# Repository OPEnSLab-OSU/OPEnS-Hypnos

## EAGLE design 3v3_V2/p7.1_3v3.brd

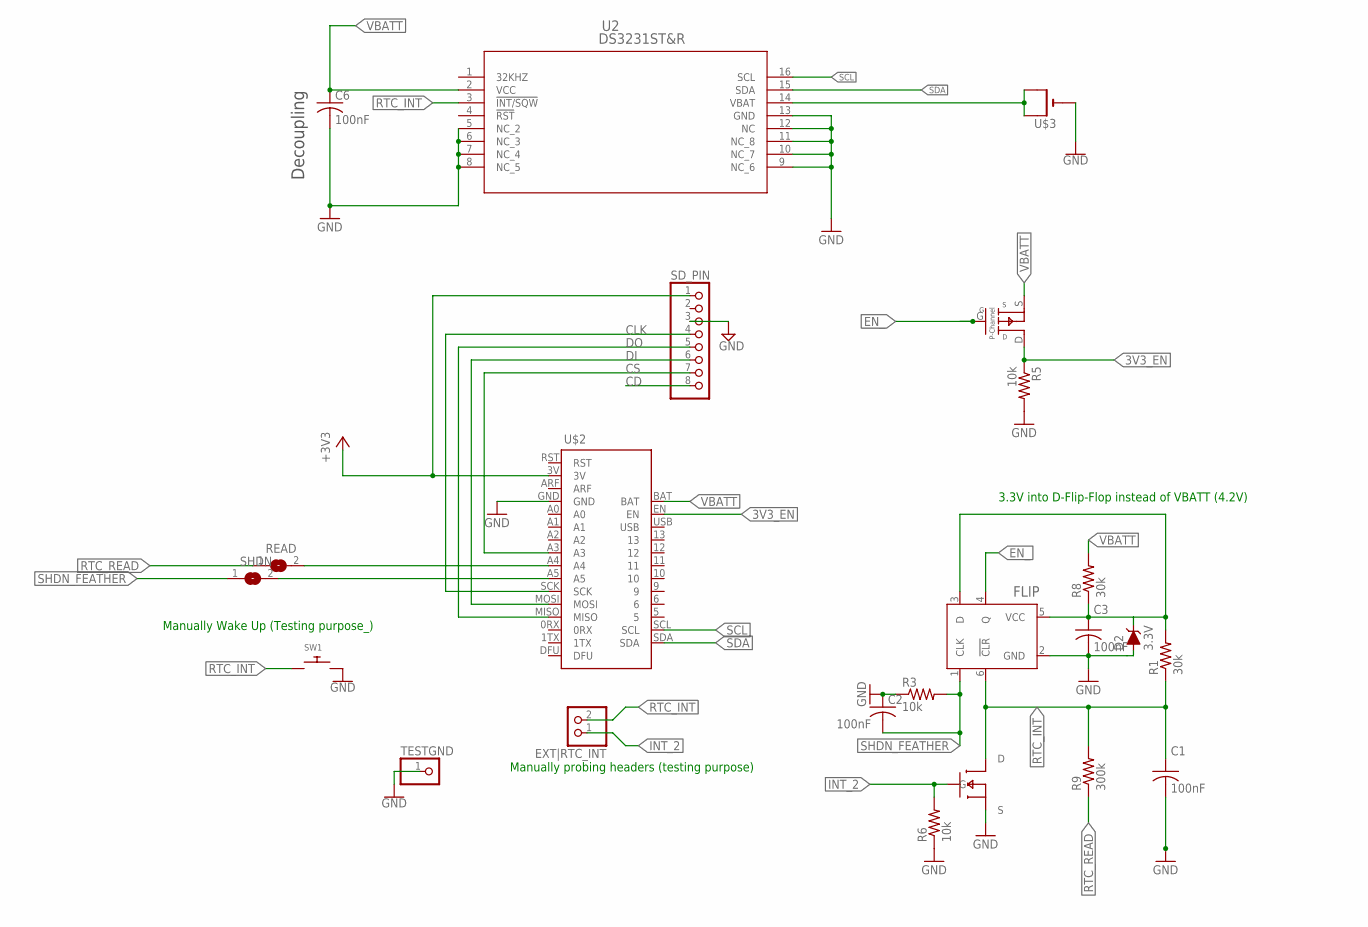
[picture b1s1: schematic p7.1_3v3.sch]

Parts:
C1, C2, C3, C6: 100nF; C1206
D2: 3.3V; SOD-323
EXT|RTC_INT: PINHD-1X2; 1X02
FLIP: SN74LVC1G175DBVR; DBV6
PMOS: MOSFET-SOT23F; SOT-23F
Q2: SSM3J3228R; SOT-23-3
R1, R8: 30k; R1206
R3, R5, R6: 10k; R1206
R9: 300k; R1206
READ: SJ
SD_PIN: PINHD-1X8BIG; 1X08-BIG
SHDN: SJ
SW1: SWITCH_PUSHBUTTONSOFTTOUCHSMD_SJ; PUSHBUTTON_SMD_SJ
TESTGND: PINHD-1X1; 1X01
U2: DS3231ST&R; 21-0042B_16
U$2: BLUEFRUIT_M0; BLUEFRUIT_MO
U$3: CR1220SMT; CR1220-SMD

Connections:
3V3_EN: Q2.D, R5.1, U$2.EN
+3V3: SD_PIN.1, U$2.3V
CD: SD_PIN.8
CLK: SD_PIN.4, U$2.SCK
CS: SD_PIN.7, U$2.A3
DI: SD_PIN.6, U$2.MOSI
DO: SD_PIN.5, U$2.MISO
EN_: FLIP.4 (Q), Q2.G
GND: C2.1, C3.2, C6.2, D2.A, FLIP.2 (GND), PMOS.S, R3.1, R5.2, R6.1, SD_PIN.3, SW1.P$2, TESTGND.1, U2.5 (NC_2), U2.6 (NC_3), U2.7 (NC_4), U2.8 (NC_5), U2.9 (NC_6), U2.10 (NC_7), U2.11 (NC_8), U2.12 (NC), U2.13 (GND), U$2.GND, U$3.-
INT_2: EXT|RTC_INT.1, PMOS.G, R6.2
unnamed: U2.14 (VBAT), U$3.+$1 (+), U$3.+$2 (+1)
unnamed: SHDN.2, U$2.A5
unnamed: READ.2, U$2.A4
unnamed: C3.1, D2.C, FLIP.3 (D), FLIP.5 (VCC), R1.2, R8.1
RTC_INT: C1.1, EXT|RTC_INT.2, FLIP.6 (!CLR), PMOS.D, R1.1, R9.2, SW1.P$1, U2.3 (!INT/SQW)
RTC_READ: R9.1, READ.1
SCL: U2.16 (SCL), U$2.SCL
SDA: U2.15 (SDA), U$2.SDA
SHDN_FEATHER: C2.2, FLIP.1 (CLK), R3.2, SHDN.1
VBATT: C6.1, Q2.S, R8.2, U2.2 (VCC), U$2.BAT

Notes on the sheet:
Decoupling
3.3V into D-Flip-Flop instead of VBATT (4.2V)
Manually Wake Up (Testing purpose_)
Manually probing headers (testing purpose)

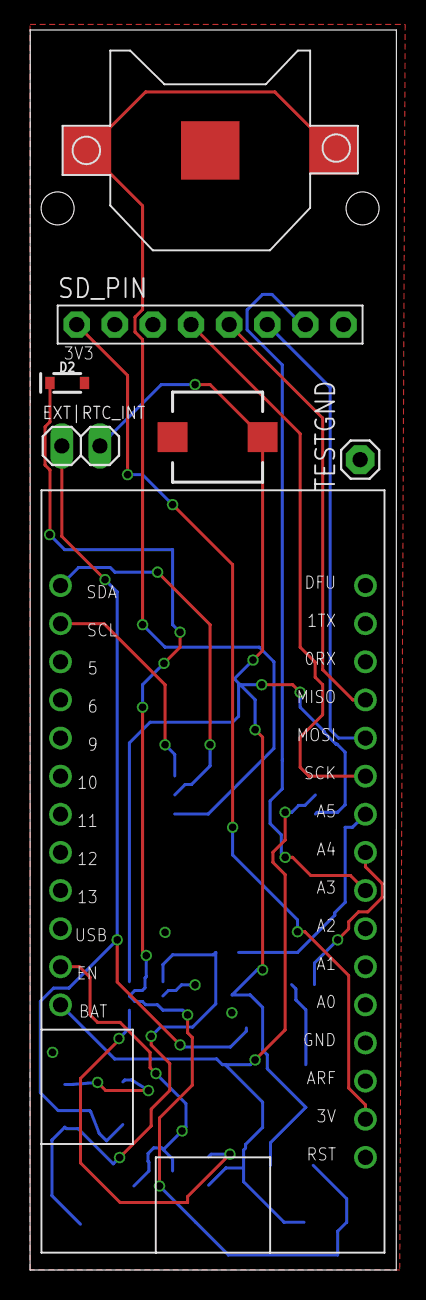
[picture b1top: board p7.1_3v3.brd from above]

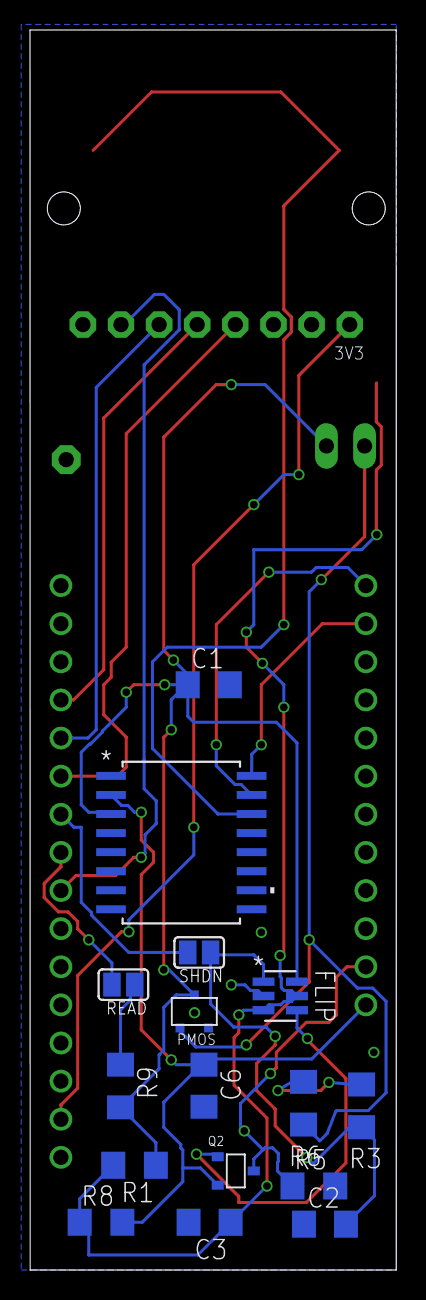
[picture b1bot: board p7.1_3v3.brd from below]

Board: 2 copper layers, 24.4 x 82.6 mm, 23 parts (16 on the bottom side), 19 nets.

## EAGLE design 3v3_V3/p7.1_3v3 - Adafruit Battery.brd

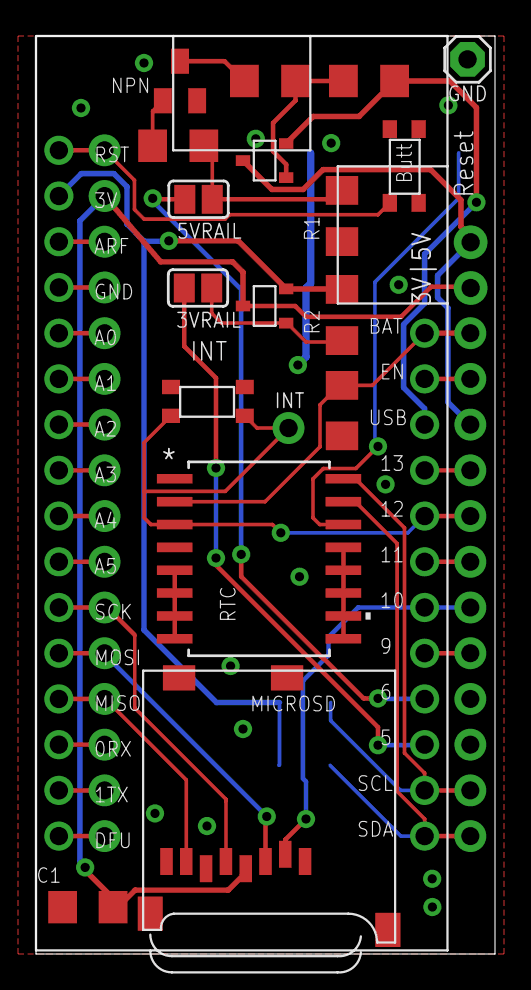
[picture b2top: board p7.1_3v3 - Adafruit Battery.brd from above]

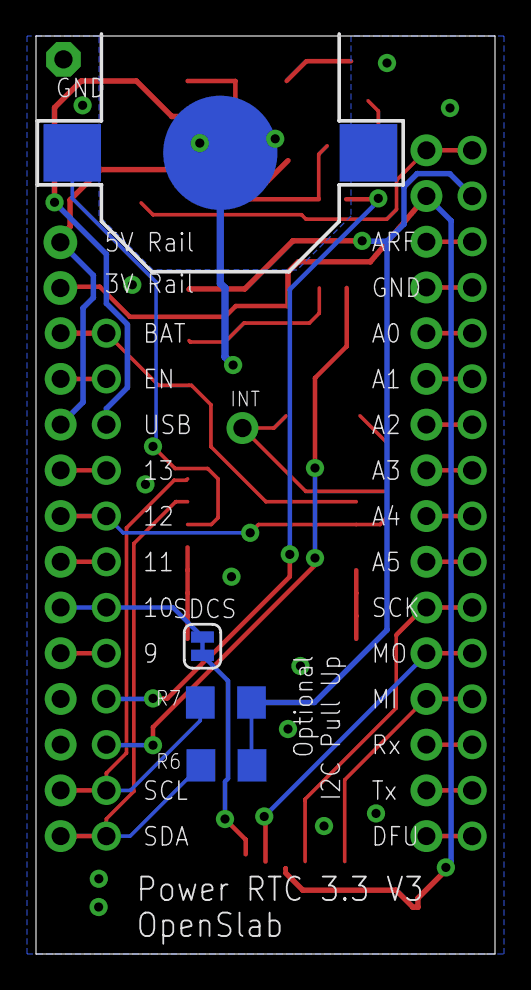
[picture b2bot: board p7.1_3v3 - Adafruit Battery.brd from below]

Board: 2 copper layers, 25.5 x 51.0 mm, 25 parts (5 on the bottom side), 37 nets.

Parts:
3VRAIL, 5VRAIL: SJ
3V|5V: 1X02_NO_SILK
B1: CR1220
C1, C3: 100nF; C1206
CS: SD Select; SMT-JUMPER_2_NC_TRACE_SILK
FEATHER: BLUEFRUIT_M0; BLUEFRUIT_MO
GND: 1X01
INT: 1X01-CLEANBIG
MICROSD: MICROSD
MS1: FEATHERWING
NPN: SOT23
PMOS1, PMOS2: SSM3J3228R; SOT-23-3
R1, R2: 30k; R1206
R3: 2M; R1206
R4: 80k; R1206
R5: 20k; R1206
R6, R7: 10k; R1206
RTC: DS3231ST&R; 21-0042B_16
U$1, U$2: PUSH_BUTTON; PUSHBUTTON_SMD

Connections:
0RX: FEATHER.0RX, MS1.14
1TX: FEATHER.1TX, MS1.15
3VRAIL: 3V|5V.1, C1.1, MICROSD.4, MS1.2, PMOS2.D
5VRAIL: 3V|5V.2, MS1.26, PMOS1.D
5VUSB: FEATHER.USB, PMOS1.S, R4.1
9: FEATHER.9, MS1.21
11: FEATHER.11, MS1.23
13: FEATHER.13, MS1.25
+3V3: FEATHER.3V, PMOS2.S, R2.2, R6.1, R7.1
A0: FEATHER.A0, MS1.5
A1: FEATHER.A1, MS1.6
A2: FEATHER.A2, MS1.7
A3: FEATHER.A3, MS1.8
A4: FEATHER.A4, MS1.9
A5: FEATHER.A5, MS1.10
ARF: FEATHER.ARF, MS1.3
CLK: FEATHER.SCK, MICROSD.5, MS1.11
CS: CS.2, MICROSD.2
DFU: FEATHER.DFU, MS1.16
DI: FEATHER.MOSI, MICROSD.3, MS1.12
DO: FEATHER.MISO, MICROSD.7, MS1.13
EN: FEATHER.EN, MS1.27
GND: B1.-, C1.2, C3.2, FEATHER.GND, GND.1, MICROSD.6, MICROSD.MT1, MICROSD.MT2, MS1.4, NPN.2, R1.2, RTC.5, RTC.6, RTC.7, RTC.8, RTC.9, RTC.10, RTC.11, RTC.12, RTC.13, U$1.1, U$1.2, U$2.3, U$2.4
unnamed: 5VRAIL.1, FEATHER.6
unnamed: B1.+$1, RTC.14
unnamed: 3VRAIL.1, FEATHER.5
unnamed: 5VRAIL.2, R1.1, R3.1
unnamed: 3VRAIL.2, PMOS2.G, R2.1
unnamed: NPN.1, R3.2
unnamed: NPN.3, R5.2
unnamed: PMOS1.G, R4.2, R5.1
unnamed: CS.1, FEATHER.10, MS1.22
RESET: FEATHER.RST, MS1.1, U$1.3, U$1.4
RTC_INT: FEATHER.12, INT.1, MS1.24, RTC.3, U$2.1, U$2.2
SCL: FEATHER.SCL, MS1.18, R7.2, RTC.16
SDA: FEATHER.SDA, MS1.17, R6.2, RTC.15
VBATT: C3.1, FEATHER.BAT, MS1.28, RTC.2

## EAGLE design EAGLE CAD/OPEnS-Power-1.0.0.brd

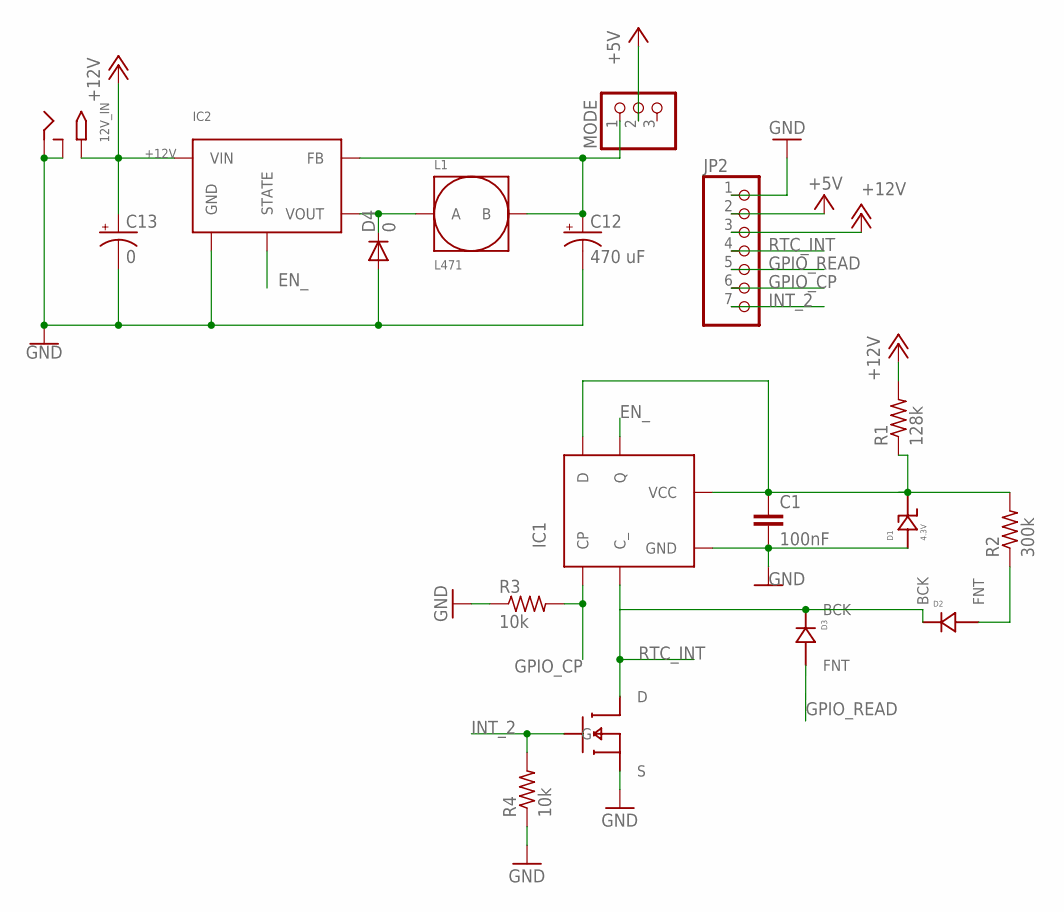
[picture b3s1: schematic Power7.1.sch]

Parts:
12V_IN: 2.1MMJACKSMT; DCJACK_2MM_SMT
C1: 100nF; C0805
C12: 470 uF; 153CLV-0810
C13: 0; 153CLV-0505
D1: 4.3V; DO-219AC
D2, D3: DIODE-DO-214AC
D4: 0; DO41-10
IC1: NC7SZ175; SC70
IC2: LM2575; TO-263
JP2: PINHD-1X7; 1X07
L1: L471; 12-12
MODE: PINHD-1X3; 1X03
Q1: MOSFET-SOT23F; SOT-23F
R1: 128k; R0805
R2: 300k; R0805
R3, R4: 10k; R0805

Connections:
5_RAW: C12.+, IC2.FB, L1.B, MODE.1
+5V: JP2.2, MODE.2
+12V: 12V_IN.PWR2 (TIP), C13.+, IC2.VIN, JP2.3, R1.2
EN_: IC1.Q, IC2.STATE
GND: 12V_IN.GND (RING), 12V_IN.GNDBREAK (RING_SW), C1.2, C12.-, C13.-, D1.BCK, D4.A, IC1.GND, IC2.GND, JP2.1, Q1.S, R3.1, R4.1
GPIO_CP: IC1.CP, JP2.6, R3.2
GPIO_READ: D3.FNT, JP2.5
INT_2: JP2.7, Q1.G, R4.2
unnamed: D4.C, IC2.VOUT, L1.A
unnamed: C1.1, D1.FNT, IC1.D, IC1.VCC, R1.1, R2.2
unnamed: D2.FNT, R2.1
RTC_INT: D2.BCK, D3.BCK, IC1.C_, JP2.4, Q1.D

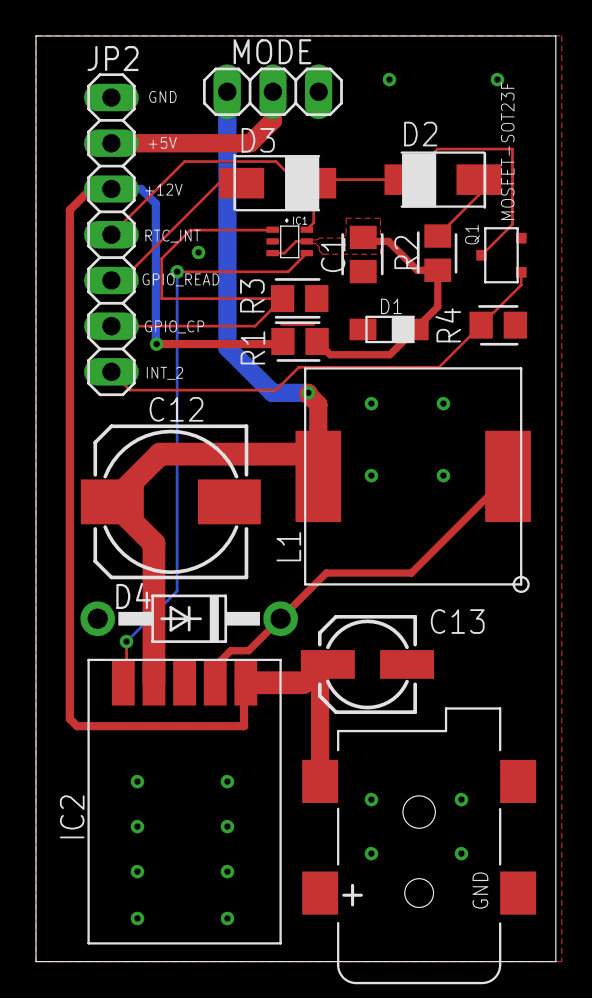
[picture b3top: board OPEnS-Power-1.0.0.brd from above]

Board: 2 copper layers, 28.9 x 51.4 mm, 18 parts (0 on the bottom side), 12 nets.

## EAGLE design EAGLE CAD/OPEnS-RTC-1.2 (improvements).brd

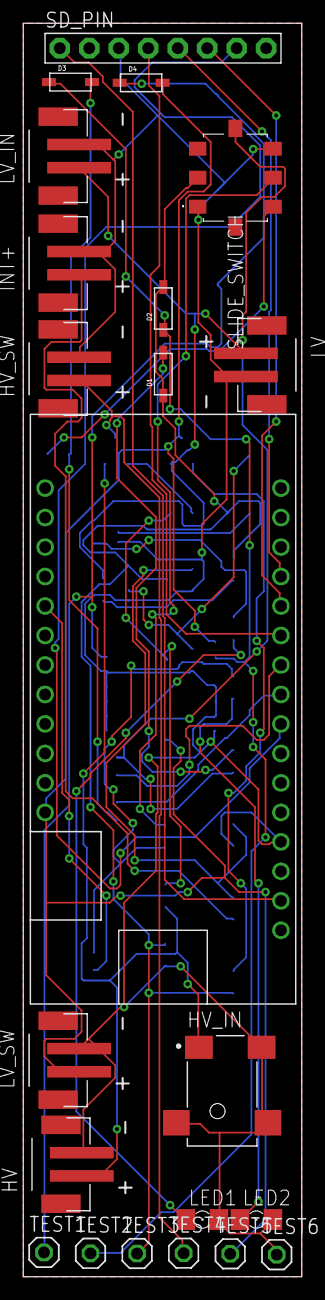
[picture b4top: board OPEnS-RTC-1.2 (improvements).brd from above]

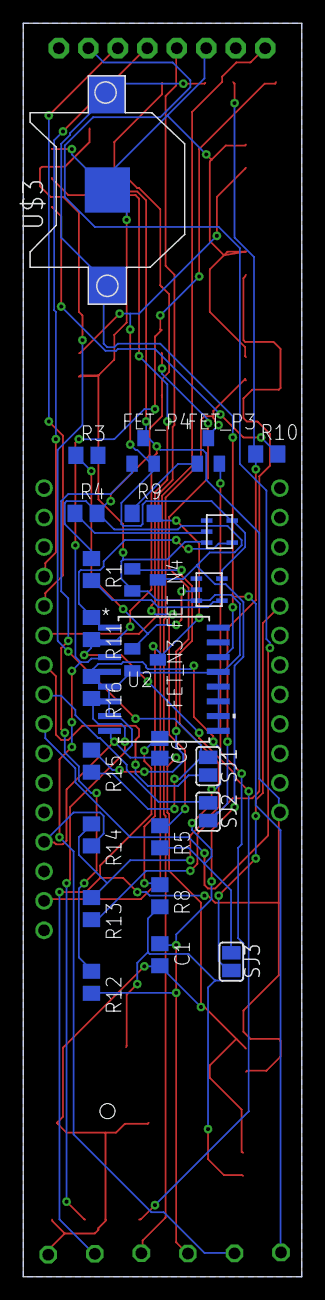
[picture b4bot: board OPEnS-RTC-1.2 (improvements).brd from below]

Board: 2 copper layers, 24.0 x 108.0 mm, 48 parts (26 on the bottom side), 33 nets.

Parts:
C1: 1 nF; C0805
C6: 100nF; C0805
D1, D2, D3, D4: SOD-123
FEATHER: BLUEFRUIT_M0; BLUEFRUIT_MO
FET_N3, FET_N4: SOT23
FET_P3, FET_P4: BSS84; SOT23
HV: JST-PH-2-SMT
HV_IN: PJ-028-SMT-TR; CUI_PJ-028-SMT-TR
HV_SW: JST-PH-2-SMT
INT+: JST-PH-2-SMT
LED1, LED2: 1206
LV: JST-PH-2-SMT
LV_IN: JST-PH-2-SMT
LV_SW: JST-PH-2-SMT
R1, R3, R4, R9, R12, R13: 500; R0805
R5, R15: 50; R0805
R8, R10, R14: 10k; R0805
R11, R16: 200; R0805
SD_PIN: 1X08-BIG
SJ1, SJ2, SJ3: SJ
SLIDE_SWITCH: SS001-S032NAPA1.2; SS001S032NAPA12
TEST1, TEST2, TEST3, TEST4, TEST5, TEST6: 1X01
U2: DS3231ST&R; 21-0042B_16
U$1, U$2: NOT_GATE; SOT753
U$3: CR1220-SMD

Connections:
+3V3: R10.2, SLIDE_SWITCH.4
+4.1V: FET_P4.2, LV.1, LV_IN.1, U$1.5, U$2.5
ALM_READ: D3.A, R10.1, SJ2.2
CLK: FEATHER.SCK, SD_PIN.4
CS: FEATHER.A3, SD_PIN.7
DI: FEATHER.MOSI, SD_PIN.6
DO: FEATHER.MISO, SD_PIN.5
GND: C1.2, C6.2, FEATHER.GND, FET_N3.2, FET_N4.2, HV.2, HV_IN.2, HV_IN.3, HV_IN.3.1, HV_SW.2, INT+.2, LED1.C, LED2.C, LV.2, LV_IN.2, LV_SW.2, R14.2, SD_PIN.3, SLIDE_SWITCH.1, SLIDE_SWITCH.6, TEST6.1, U2.5, U2.6, U2.7, U2.8, U2.9, U2.10, U2.11, U2.12, U2.13, U$1.3, U$2.3, U$3.-
INT+: INT+.1, R13.2
LOAD_HV: FET_P3.3, HV_SW.1, TEST4.1
LOAD_LV: C6.1, D4.A, FEATHER.BAT, FET_P4.3, LV_SW.1, TEST5.1, U2.2
unnamed: R11.1, U$1.4
unnamed: R4.1, U$1.2
unnamed: R1.2, U$2.4
unnamed: FET_N3.1, R3.1, U$2.2
unnamed: FET_N3.3, R8.1, R9.2
unnamed: R5.1, SLIDE_SWITCH.5
unnamed: FET_P3.1, R9.1
unnamed: LED1.A, R11.2
unnamed: FET_P4.1, R12.1
unnamed: D1.A, R15.1
unnamed: FET_N4.1, R13.1, R14.1
unnamed: LED2.A, R16.2
unnamed: FEATHER.A4, SJ2.1
unnamed: FEATHER.A5, SJ1.2
unnamed: FEATHER.9, SJ3.2
OVR_READ: R5.2, R16.1, SJ3.1
RTC_ALM: D2.C, D3.C, TEST2.1, U2.3
SHDN: R15.2, SJ1.1, SLIDE_SWITCH.8
VCC: FEATHER.3V, SD_PIN.1
VCC_HV: FET_P3.2, HV.1, HV_IN.1, R8.2
V_BACKUP: D4.C, TEST1.1, U2.14, U$3.+$1, U$3.+$2
V_LATCH: C1.1, D1.C, D2.A, FET_N4.3, R1.1, R4.2, R12.2, SLIDE_SWITCH.2, TEST3.1

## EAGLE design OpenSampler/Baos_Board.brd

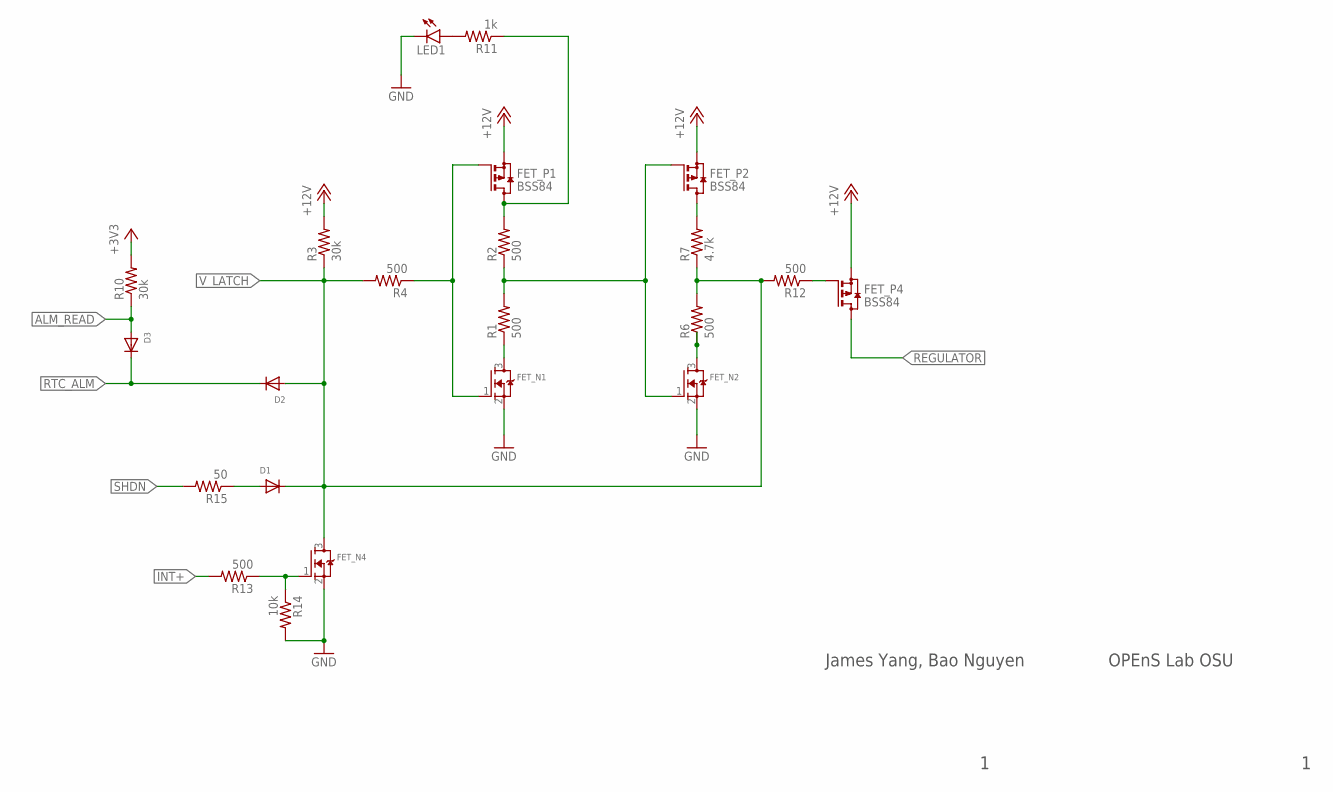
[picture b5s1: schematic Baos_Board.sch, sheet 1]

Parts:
D1, D2, D3: DIODESOD-123; SOD-123
FET_N1, FET_N2, FET_N4: MOSFET-NREFLOW; SOT23
FET_P1, FET_P2, FET_P4: BSS84; SOT23
LED1: LEDSMT1206; 1206
R1, R2, R4, R6, R12, R13: 500; R0805
R3, R10: 30k; R0805
R7: 4.7k; R0805
R11: 1k; R0805
R14: 10k; R0805
R15: 50; R0805

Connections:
+3V3: R10.2; also elsewhere on the board
+12V: FET_P1.2 (S), FET_P2.2 (S), FET_P4.2 (S), R3.2; also elsewhere on the board
ALM_READ: D3.A, R10.1; also elsewhere on the board
GND: FET_N1.2 (S), FET_N2.2 (S), FET_N4.2 (S), LED1.C, R14.2; also elsewhere on the board
INT+: R13.2
unnamed: FET_P1.3 (D), R2.2, R11.1
unnamed: FET_N1.3 (D), R1.1
unnamed: FET_N1.1 (G), FET_P1.1 (G), R4.1
unnamed: FET_N2.1 (G), FET_P2.1 (G), R1.2, R2.1
unnamed: FET_P2.3 (D), R7.2
unnamed: FET_N2.3 (D), R6.1
unnamed: LED1.A, R11.2
unnamed: FET_P4.1 (G), R12.1
unnamed: D1.A, R15.1
unnamed: FET_N4.1 (G), R13.1, R14.1
REGULATOR: FET_P4.3 (D); also elsewhere on the board
RTC_ALM: D2.C, D3.C; also elsewhere on the board
SHDN: R15.2; also elsewhere on the board
V_LATCH: D1.C, D2.A, FET_N4.3 (D), R3.1, R4.2, R6.2, R7.1, R12.2; also elsewhere on the board

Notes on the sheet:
James Yang, Bao Nguyen
OPEnS Lab OSU

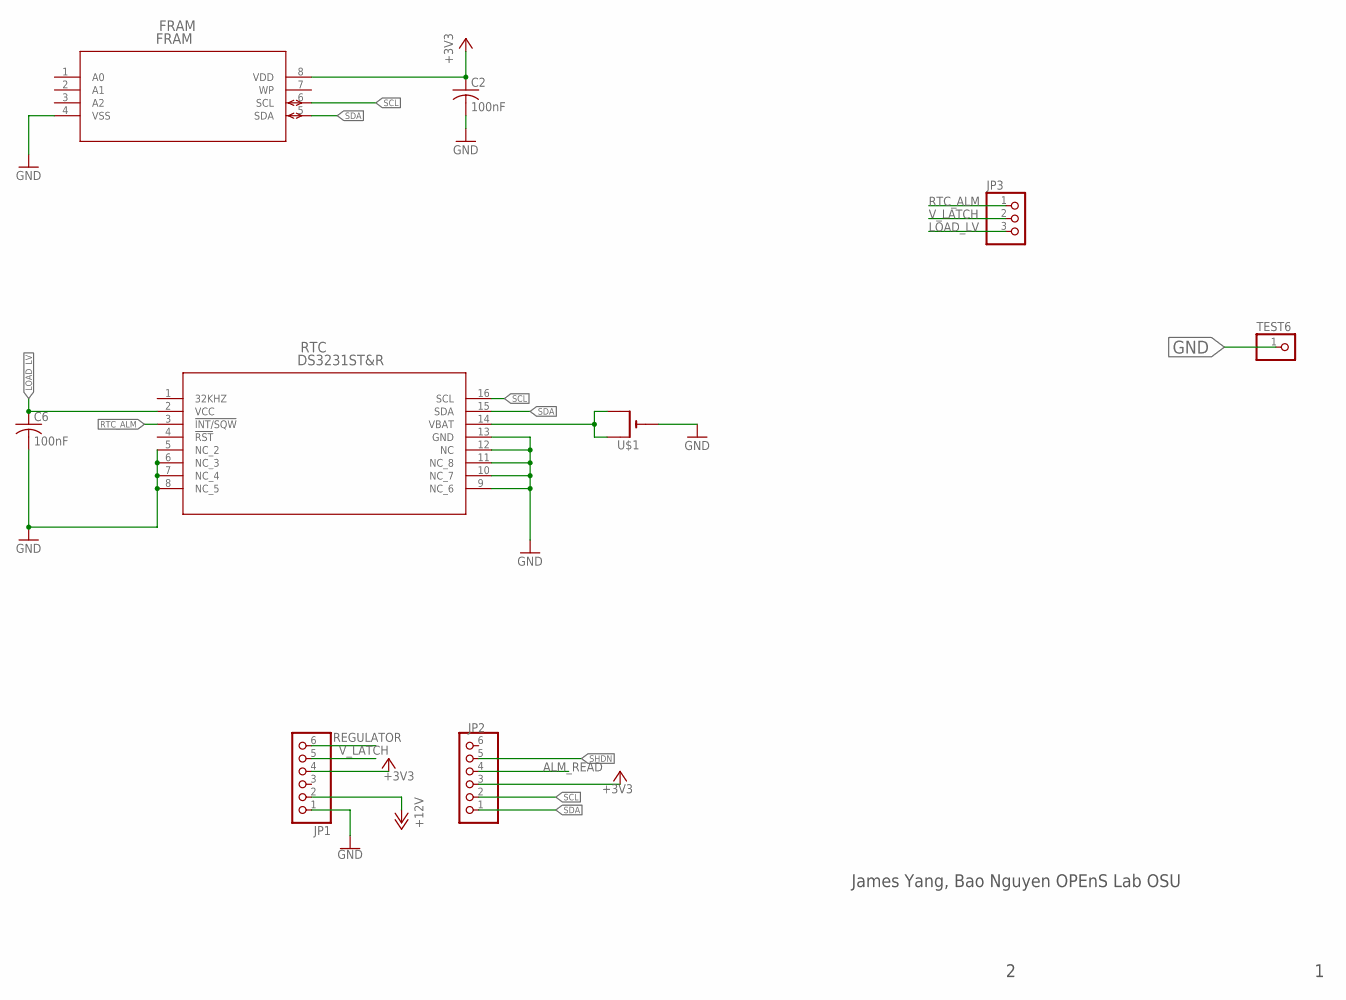
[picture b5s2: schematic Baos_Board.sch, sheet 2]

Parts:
C2, C6: 100nF; C0805
FRAM: FRAM; FPT-8P-M02
JP1, JP2: PINHD-1X6; 1X06
JP3: PINHD-1X3; 1X03
RTC: DS3231ST&R; 21-0042B_16
TEST6: PINHD-1X1; 1X01
U$1: CR1220SMT; CR1220-SMD

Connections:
+3V3: C2.1, FRAM.8 (VDD), JP1.4, JP2.3; also elsewhere on the board
+12V: JP1.2; also elsewhere on the board
ALM_READ: JP2.4; also elsewhere on the board
GND: C2.2, C6.2, FRAM.4 (VSS), JP1.1, RTC.5 (NC_2), RTC.6 (NC_3), RTC.7 (NC_4), RTC.8 (NC_5), RTC.9 (NC_6), RTC.10 (NC_7), RTC.11 (NC_8), RTC.12 (NC), RTC.13 (GND), TEST6.1, U$1.-; also elsewhere on the board
LOAD_LV: C6.1, JP3.3, RTC.2 (VCC)
unnamed: RTC.14 (VBAT), U$1.+$1 (+), U$1.+$2 (+1)
REGULATOR: JP1.6; also elsewhere on the board
RTC_ALM: JP3.1, RTC.3 (!INT/SQW); also elsewhere on the board
SCL: FRAM.6 (SCL), JP2.2, RTC.16 (SCL)
SDA: FRAM.5 (SDA), JP2.1, RTC.15 (SDA)
SHDN: JP2.5; also elsewhere on the board
V_LATCH: JP1.5, JP3.2; also elsewhere on the board

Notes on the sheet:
James Yang, Bao Nguyen OPEnS Lab OSU

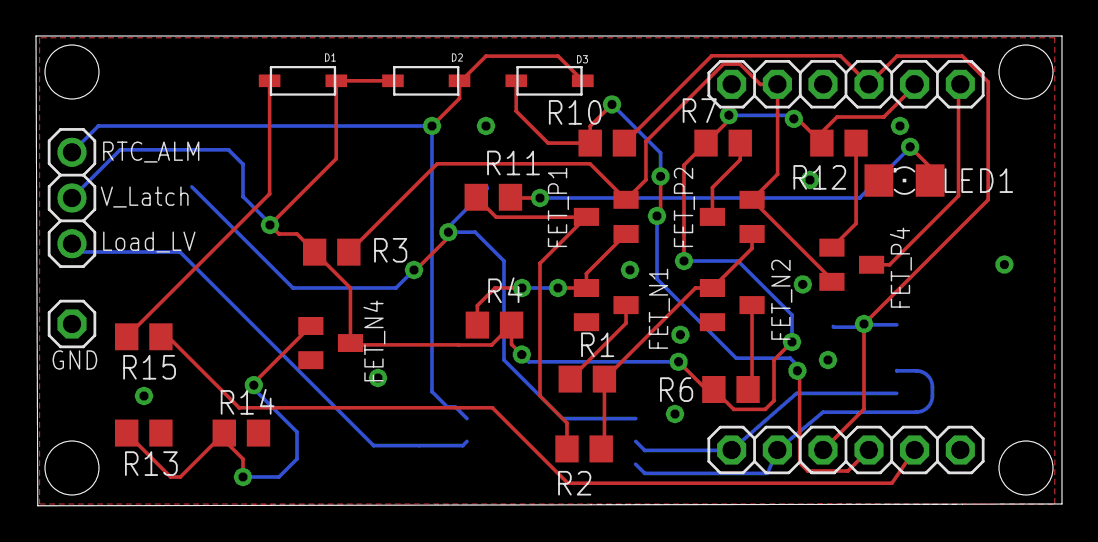
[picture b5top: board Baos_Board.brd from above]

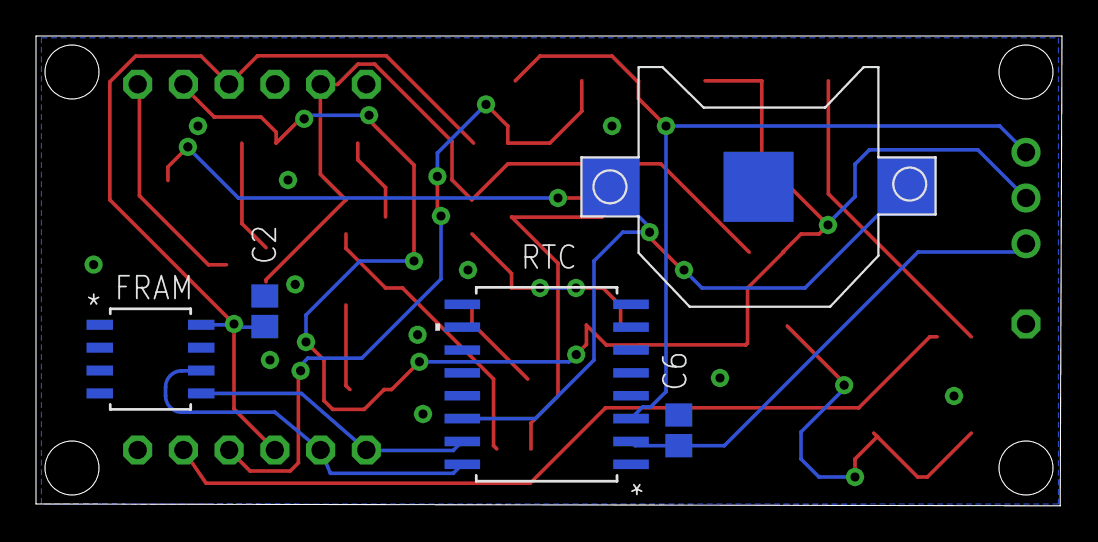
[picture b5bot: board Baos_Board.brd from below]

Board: 2 copper layers, 57.0 x 26.1 mm, 31 parts (5 on the bottom side), 22 nets.

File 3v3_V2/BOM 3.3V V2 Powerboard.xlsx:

Part Name | Part Number | Amount | Link | Footprint | Cost
Micro SD Pinout | 254.0 | 1.0 | Adafruit | 1X08-BIG | 7.5
DS3231 RTC | DS3231SN#T&RCT-ND | 1.0 | Adafruit | 16-SOP | 9.05
Battery Holder | 36-3000CT-ND | 1.0 | Digikey | CR1220-SMD | 0.91
500 Ohm Resistor (475 Ohm) | 541-3306-1-ND | 3.0 | Digikey | R1206 (Version 1) | 0.1
10k Ohm Resistor | CRT1206-BY-1002ELFCT-ND | 3.0 | Digikey | R1206 (Version 1) | 0.53
Capacitor 100nF | 1276-1017-1-ND | 3.0 | Digikey | C1206 (Version 1) | 0.12
Feather M0 | 2772.0 | 1.0 | Adafruit | BLUEFRUIT_MO | 19.95
30k Ohm Resistor | P30KDBCT-ND | 2.0 | Digikey | R1206 (Version 1) | 0.35
Pin Headers | 732-5315-ND | 1.0 | Digikey | 1X02 (Version 1) | 0.13
D-Flip-Flop | 296-17617-1-ND | 1.0 | Digikey | DBV6 | 0.37
1k Ohm Resistor | 311-1KMCT-ND | 1.0 | Digikey | R1206 (Version 1) | 0.1
PMOS | BSS84-FDICT-ND | 1.0 | Digikey | SOT-23-3 | 0.24
NMOS | BSS131H6327XTSA1CT-ND | 1.0 | Digikey | SOT-23-3 | 0.47
300k Ohm Resistor | RHM300KAICT-ND | 1.0 | Digikey | R1206 (Version 1) | 0.21
Push Button | 1400.0 | 1.0 | Pololu | PUSHBUTTON_SMD_SJ (Version 1) | 0.99

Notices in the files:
parts and their libraries:
SparkFun-DiscreteSemi: Licensing: Creative Commons ShareAlike 4.0 International - https://creativecommons.org/licenses/by-sa/4.0
microbuilder: This work is placed in the public domain, and may be freely used for commercial and non-commercial work with the following conditions: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
